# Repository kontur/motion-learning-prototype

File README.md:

#Motion learning
Prototype for wearable device enhancing motion based learning through sensory feedback.

The idea of this wearable device is to allow the wearer to rely on a multitude of additional sensory information when learning or repeating physical motion. This prototype is designed as a wrist-worn band that gives light, sound and vibration feedback.

Furthermore, the planned desktop interface allows users to record, compare and visualize their movement patterns.

##WIP
Codebase and physical design currently heavily WIP.

##Credits
Many parts of this project are based on open software or hardware. Arduino, Processing and Eagle have been used for the various aspects of the project. In more details:

* The led shield uses the [Adafruit PWM servo driver library](https://github.com/adafruit/Adafruit-PWM-Servo-Driver-Library)
* The Sparkfun IMU shields and their libraries [LSM9](https://github.com/sparkfun/LSM9DS0_Breakout) and [6DoF](https://github.com/sparkfun/IMU_Digital_Combo_Board)
* The project uses [this](http://bildr.org/2012/03/stable-orientation-digital-imu-6dof-arduino/) modification of [Varesano's FreeIMU](www.varesano.net/projects/hardware/FreeIMU) libraries for motion sensor reading
* [HSBColor](https://github.com/julioterra/HSB_Color) library for Arduino for color conversions
* [Toxiclibs](http://toxiclibs.org/) was used on the Processing visualization
* [controlP5](http://www.sojamo.de/libraries/controlP5/) was used in the Processing interface
* [Javastat](http://www2.thu.edu.tw/~wenwei/javastat/doc/) libraries were used for some portions in the software dealing with comparing motion patterns

###Authors
Johannes Neumeier, Jana Pejoska

###Acknowledgments
Project created in spring 2015 at Aalto Media Lab, in the course Prototyping Experience under guidance from Michihito Mizutani.

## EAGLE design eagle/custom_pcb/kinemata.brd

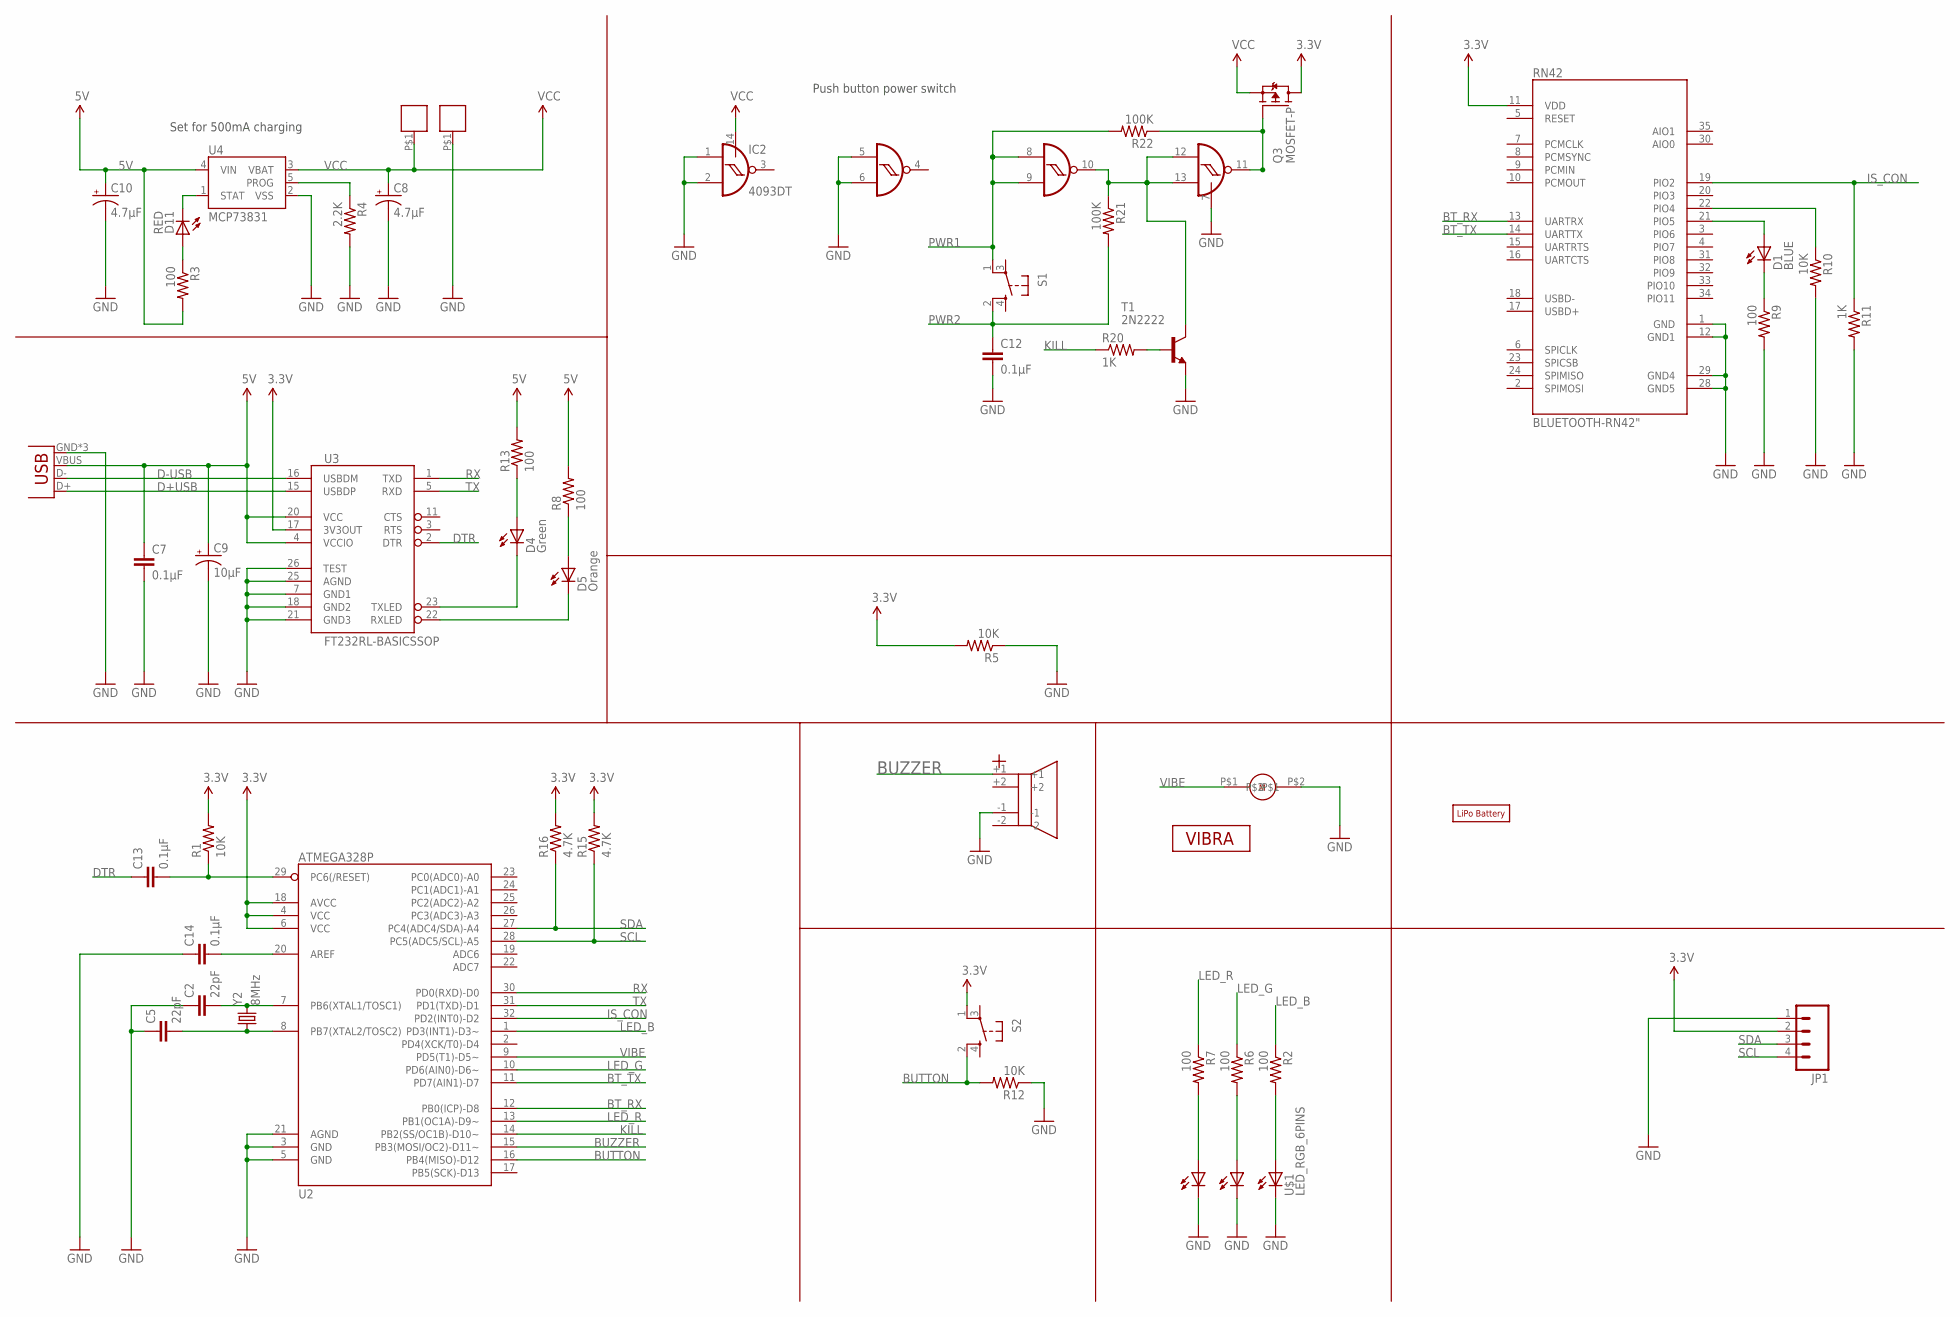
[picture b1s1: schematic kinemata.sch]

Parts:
BAT+2: LIPO_PAD
BAT-1: LIPO_PAD
C2, C5: 22pF; 1206
C7, C12, C13, C14: 0.1µF; 1206
C8, C10: 4.7µF; EIA3216
C9: 10µF; EIA3216
D1: BLUE; LED-1206
D4: Green; LED-1206
D5: Orange; LED-1206
D11: RED; LED-1206
IC2: 4093DT; MC14093B-TSSOP14
JP1: M04LONGPADS; 1X04_LONGPADS
JP6: USB-MICROB
Q3: MOSFET-P; SOT23
R1, R5, R10, R12: 10K; 1206
R2, R3, R6, R7, R8, R9, R13: 100; 1206
R4: 2.2K; 1206
R11, R20: 1K; 1206
R15, R16: 4.7K; 1206
R21, R22: 100K; 1206
RN42: BLUETOOTH-RN42"; RN42
S1, S2: TAC_SWITCH_SIDEWAY; TACTILE_SWITCH_ANGLE_SMD
T1: 2N2222; TO92-EBC-OVAL
U2: ATMEGA328P; TQFP32-08
U3: FT232RL-BASICSSOP; SSOP28DB
U4: MCP73831; SOT23-5
U$1: LED_RGB_6PINS
U$2: LIPO_BATTERY110MAH; LIPO_BATTERY_110MAH
U$3: BUZZER_4PINS; FARNELL_BUZZER_MAGNETIC_SMD_3V_2215091
U$4: VIBRATION_MOTOR_SHAPE
U$5: VIBRATION_MOTOR; VIBRATION_MOTOR_CABLE
Y2: 8MHz; CRYSTAL_8MHZ_SMD_FARNELL_2101329

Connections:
3.3V: JP1.2, Q3.3 (D), R1.2, R5.2, R15.2, R16.2, RN42.11 (VDD), S2.1 (A2), U2.4 (VCC), U2.6 (VCC), U2.18 (AVCC), U3.17 (3V3OUT)
5V: C7.1, C9.A (+), C10.A (+), JP6.VBUS, R3.2, R8.2, R13.2, U3.4 (VCCIO), U3.20 (VCC), U4.4 (VIN)
BT_RX: RN42.13 (UARTRX), U2.12 (PB0(ICP)-D8)
BT_TX: RN42.14 (UARTTX), U2.11 (PD7(AIN1)-D7)
BUTTON: R12.2, S2.2 (B2), U2.16 (PB4(MISO)-D12)
BUZZER: U2.15 (PB3(MOSI/OC2)-D11~), U$3.+1
D+USB: JP6.D+, U3.15 (USBDP)
D-USB: JP6.D-, U3.16 (USBDM)
DTR: C13.1, U3.2 (DTR)
GND: BAT-1.P$1, C2.1, C5.1, C7.2, C8.C (-), C9.C (-), C10.C (-), C12.2, C14.1, IC2.1, IC2.2, IC2.5, IC2.6, IC2.7, JP1.1, JP6.GND, JP6.MT1 (GND), JP6.MT2 (GND), R4.2, R5.1, R9.2, R10.2, R11.2, R12.1, RN42.1 (GND), RN42.12 (GND1), RN42.28 (GND5), RN42.29 (GND4), T1.E, U2.3 (GND), U2.5 (GND), U2.21 (AGND), U3.7 (GND1), U3.18 (GND2), U3.21 (GND3), U3.25 (AGND), U3.26 (TEST), U4.2 (VSS), U$1.BC, U$1.GC, U$1.RC, U$3.-1, U$5.P$2
IS_CON: R11.1, RN42.19 (PIO2), U2.32 (PD2(INT0)-D2)
KILL: R20.1, U2.14 (PB2(SS/OC1B)-D10~)
LED_B: R2.1, U2.1 (PD3(INT1)-D3~)
LED_G: R6.1, U2.10 (PD6(AIN0)-D6~)
LED_R: R7.1, U2.13 (PB1(OC1A)-D9~)
unnamed: R7.2, U$1.BA
unnamed: R2.2, U$1.GA
unnamed: D11.A, R3.1
unnamed: R6.2, U$1.RA
unnamed: D4.A, R13.1
unnamed: D5.A, R8.1
unnamed: R10.1, RN42.22 (PIO4)
unnamed: D1.A, RN42.21 (PIO5)
unnamed: C5.2, U2.8 (PB7(XTAL2/TOSC2)), Y2.P$1 (1)
unnamed: C2.2, U2.7 (PB6(XTAL1/TOSC1)), Y2.P$2 (2)
unnamed: D1.C, R9.1
unnamed: C13.2, R1.1, U2.29 (PC6(/RESET))
unnamed: C14.2, U2.20 (AREF)
unnamed: IC2.10, IC2.12, IC2.13, R21.1, T1.C
unnamed: R20.2, T1.B
unnamed: IC2.11, Q3.1 (G), R22.1
PROG: R4.1, U4.5 (PROG)
PWR1: IC2.8, IC2.9, R22.2, S1.1 (A2)
PWR2: C12.1, R21.2, S1.2 (B2)
RX: U2.30 (PD0(RXD)-D0), U3.1 (TXD)
RXLED: D5.C, U3.22 (RXLED)
SCL: JP1.4, R15.1, U2.28 (PC5(ADC5/SCL)-A5)
SDA: JP1.3, R16.1, U2.27 (PC4(ADC4/SDA)-A4)
STAT: D11.C, U4.1 (STAT)
TX: U2.31 (PD1(TXD)-D1), U3.5 (RXD)
TXLED: D4.C, U3.23 (TXLED)
VCC: BAT+2.P$1, C8.A (+), IC2.14, Q3.2 (S), U4.3 (VBAT)
VIBE: U2.9 (PD5(T1)-D5~), U$5.P$1

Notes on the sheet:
Set for 500mA charging
Push button power switch

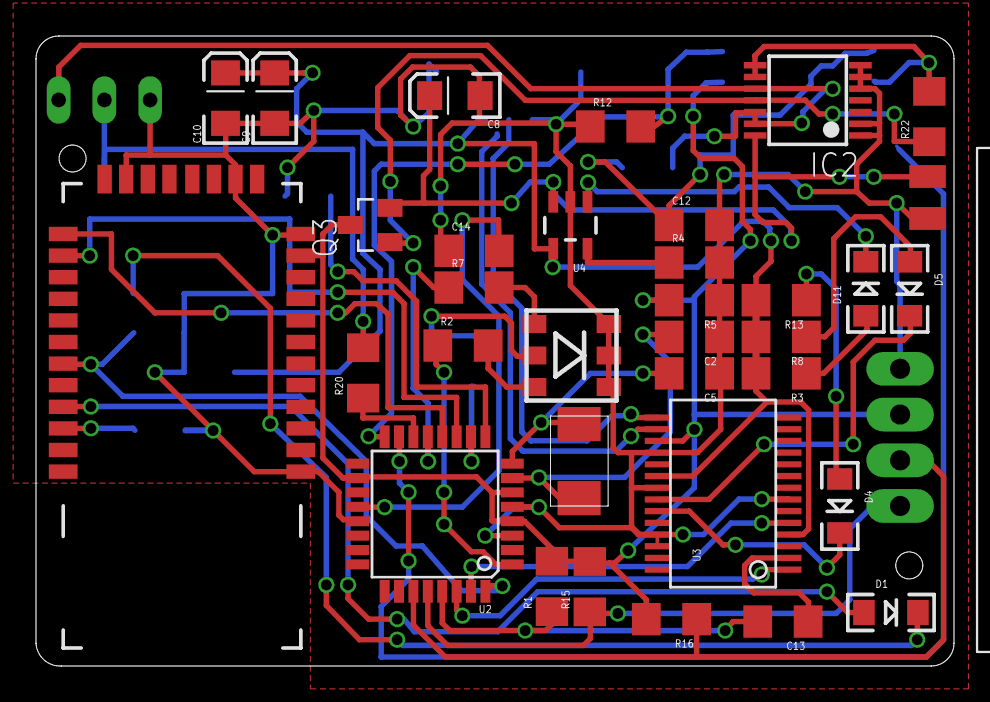
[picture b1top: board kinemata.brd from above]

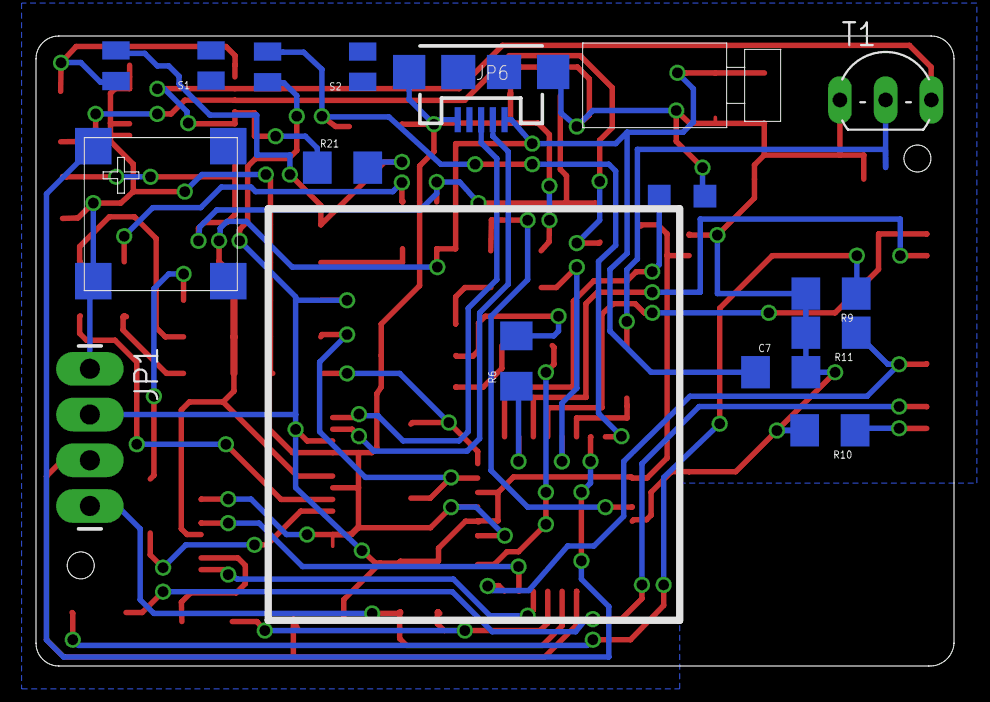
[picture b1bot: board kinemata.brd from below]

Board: 2 copper layers, 51.0 x 35.0 mm, 50 parts (14 on the bottom side), 43 nets.

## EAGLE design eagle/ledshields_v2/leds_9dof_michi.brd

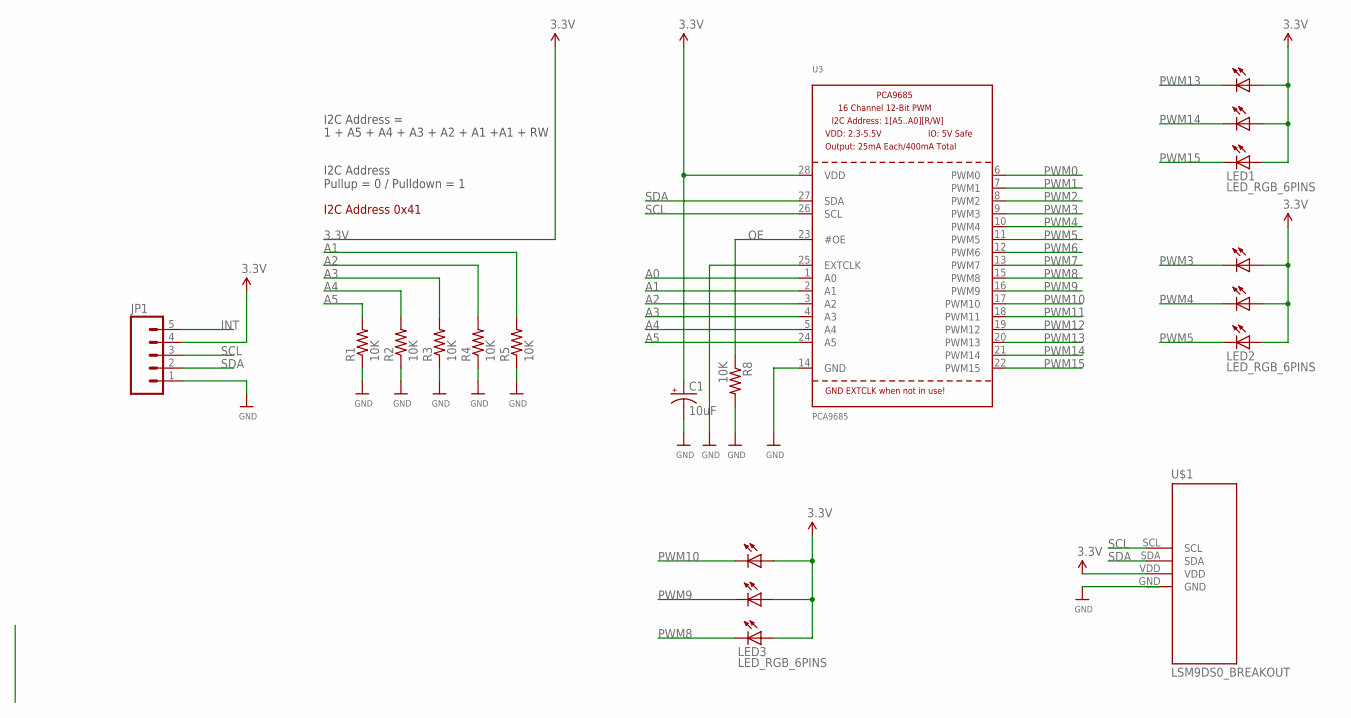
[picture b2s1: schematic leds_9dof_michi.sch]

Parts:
C1: 10uF; EIA3216
JP1: M05PTH; 1X05
LED1, LED2, LED3: LED_RGB_6PINS
R1, R2, R3, R4, R5, R8: 10K; 1206
U3: PCA9685; TSSOP28
U$1: LSM9DS0_BREAKOUT

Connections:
3.3V: C1.A (+), JP1.4, LED1.BA, LED1.GA, LED1.RA, LED2.BA, LED2.GA, LED2.RA, LED3.BA, LED3.GA, LED3.RA, U3.28 (VDD), U$1.VDD
A0: U3.1 (A0)
A1: R5.2, U3.2 (A1)
A2: R4.2, U3.3 (A2)
A3: R3.2, U3.4 (A3)
A4: R2.2, U3.5 (A4)
A5: R1.2, U3.24 (A5)
GND: C1.C (-), JP1.1, R1.1, R2.1, R3.1, R4.1, R5.1, R8.2, U3.14 (GND), U3.25 (EXTCLK), U$1.GND
INT: JP1.5
OE: R8.1, U3.23 (#OE)
PWM0: U3.6 (PWM0)
PWM1: U3.7 (PWM1)
PWM2: U3.8 (PWM2)
PWM3: LED2.BC, U3.9 (PWM3)
PWM4: LED2.RC, U3.10 (PWM4)
PWM5: LED2.GC, U3.11 (PWM5)
PWM6: U3.12 (PWM6)
PWM7: U3.13 (PWM7)
PWM8: LED3.GC, U3.15 (PWM8)
PWM9: LED3.RC, U3.16 (PWM9)
PWM10: LED3.BC, U3.17 (PWM10)
PWM11: U3.18 (PWM11)
PWM12: U3.19 (PWM12)
PWM13: LED1.BC, U3.20 (PWM13)
PWM14: LED1.RC, U3.21 (PWM14)
PWM15: LED1.GC, U3.22 (PWM15)
SCL: JP1.3, U3.26 (SCL), U$1.SCL
SDA: JP1.2, U3.27 (SDA), U$1.SDA

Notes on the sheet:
1 + A5 + A4 + A3 + A2 + A1 +A1 + RW
I2C Address =
I2C Address Pullup = 0 / Pulldown = 1
I2C Address 0x41

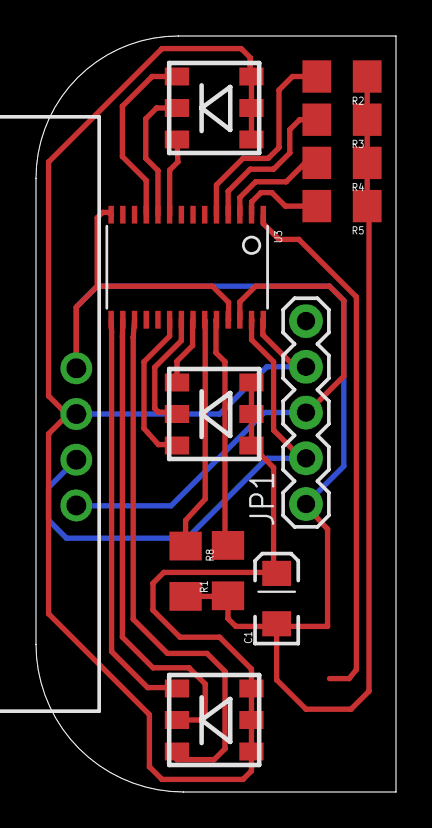
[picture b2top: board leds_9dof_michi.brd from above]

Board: 2 copper layers, 20.0 x 42.0 mm, 13 parts (0 on the bottom side), 19 nets.

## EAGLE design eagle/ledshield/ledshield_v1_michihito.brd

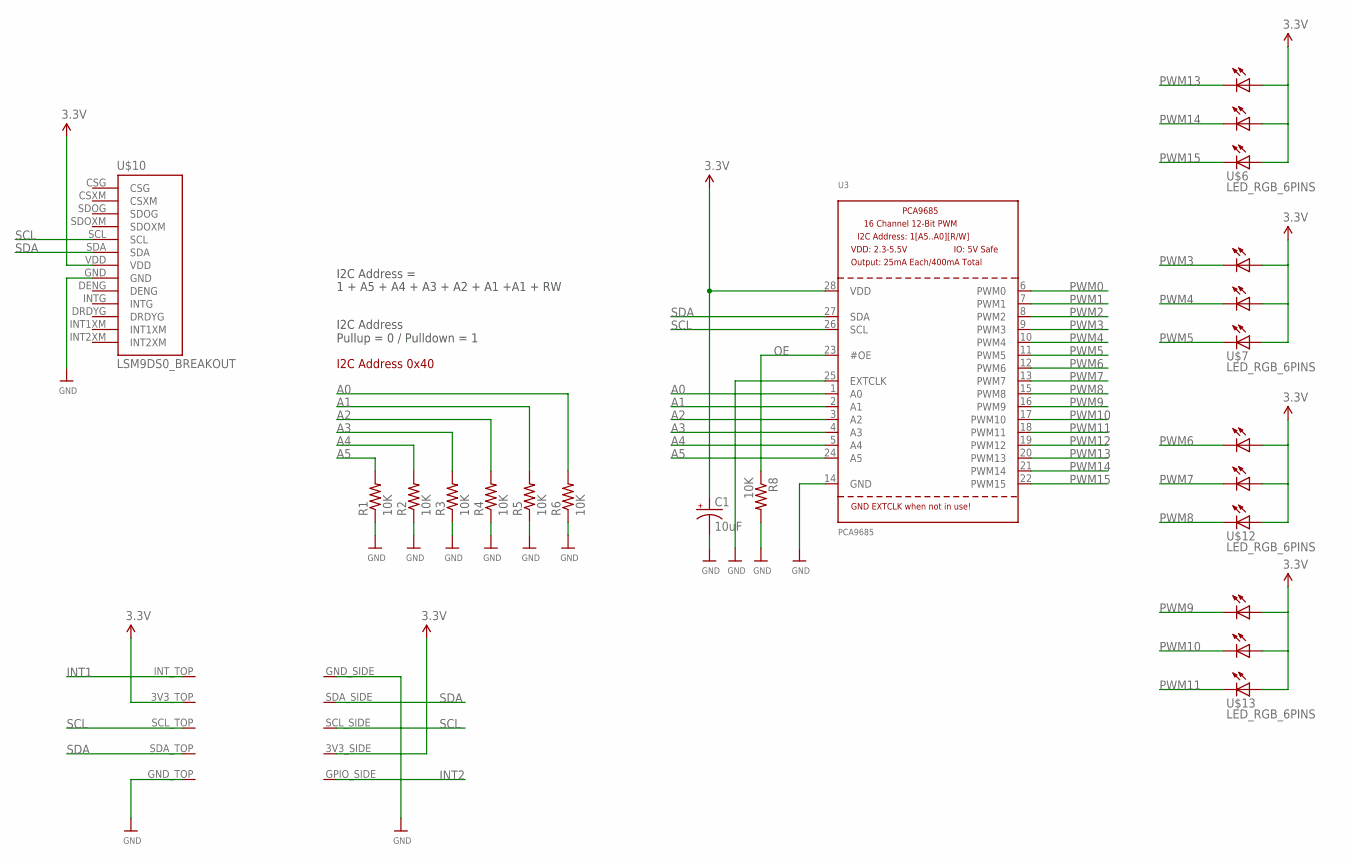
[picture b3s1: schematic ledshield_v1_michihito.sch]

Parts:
C1: 10uF; EIA3216
R1, R2, R3, R4, R5, R6, R8: 10K; 1206
U3: PCA9685; TSSOP28
U$1: IOT_MODULE_MAIN_V2_PTH; IOT_MODULE_MAIN_V3_PTH
U$6, U$7, U$12, U$13: LED_RGB_6PINS
U$10: LSM9DS0_BREAKOUT

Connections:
3.3V: C1.A (+), U3.28 (VDD), U$1.3V3_SIDE, U$1.3V3_TOP, U$6.BA, U$6.GA, U$6.RA, U$7.BA, U$7.GA, U$7.RA, U$10.VDD, U$12.BA, U$12.GA, U$12.RA, U$13.BA, U$13.GA, U$13.RA
A0: R6.2, U3.1 (A0)
A1: R5.2, U3.2 (A1)
A2: R4.2, U3.3 (A2)
A3: R3.2, U3.4 (A3)
A4: R2.2, U3.5 (A4)
A5: R1.2, U3.24 (A5)
GND: C1.C (-), R1.1, R2.1, R3.1, R4.1, R5.1, R6.1, R8.2, U3.14 (GND), U3.25 (EXTCLK), U$1.GND_SIDE, U$1.GND_TOP, U$10.GND
INT1: U$1.INT_TOP
INT2: U$1.GPIO_SIDE
OE: R8.1, U3.23 (#OE)
PWM0: U3.6 (PWM0)
PWM1: U3.7 (PWM1)
PWM2: U3.8 (PWM2)
PWM3: U3.9 (PWM3), U$7.BC
PWM4: U3.10 (PWM4), U$7.RC
PWM5: U3.11 (PWM5), U$7.GC
PWM6: U3.12 (PWM6), U$12.BC
PWM7: U3.13 (PWM7), U$12.RC
PWM8: U3.15 (PWM8), U$12.GC
PWM9: U3.16 (PWM9), U$13.BC
PWM10: U3.17 (PWM10), U$13.RC
PWM11: U3.18 (PWM11), U$13.GC
PWM12: U3.19 (PWM12)
PWM13: U3.20 (PWM13), U$6.BC
PWM14: U3.21 (PWM14), U$6.RC
PWM15: U3.22 (PWM15), U$6.GC
SCL: U3.26 (SCL), U$1.SCL_SIDE, U$1.SCL_TOP, U$10.SCL
SDA: U3.27 (SDA), U$1.SDA_SIDE, U$1.SDA_TOP, U$10.SDA

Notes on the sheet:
1 + A5 + A4 + A3 + A2 + A1 +A1 + RW
I2C Address =
I2C Address Pullup = 0 / Pulldown = 1
I2C Address 0x40

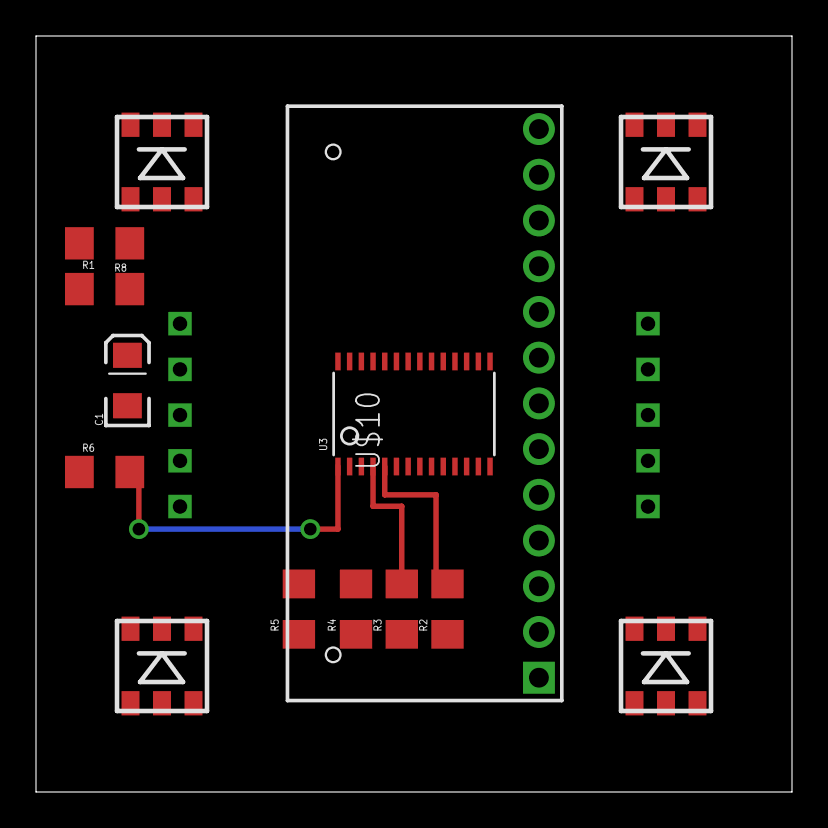
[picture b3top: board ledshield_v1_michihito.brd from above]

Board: 2 copper layers, 42.0 x 42.0 mm, 15 parts (0 on the bottom side), 23 nets.

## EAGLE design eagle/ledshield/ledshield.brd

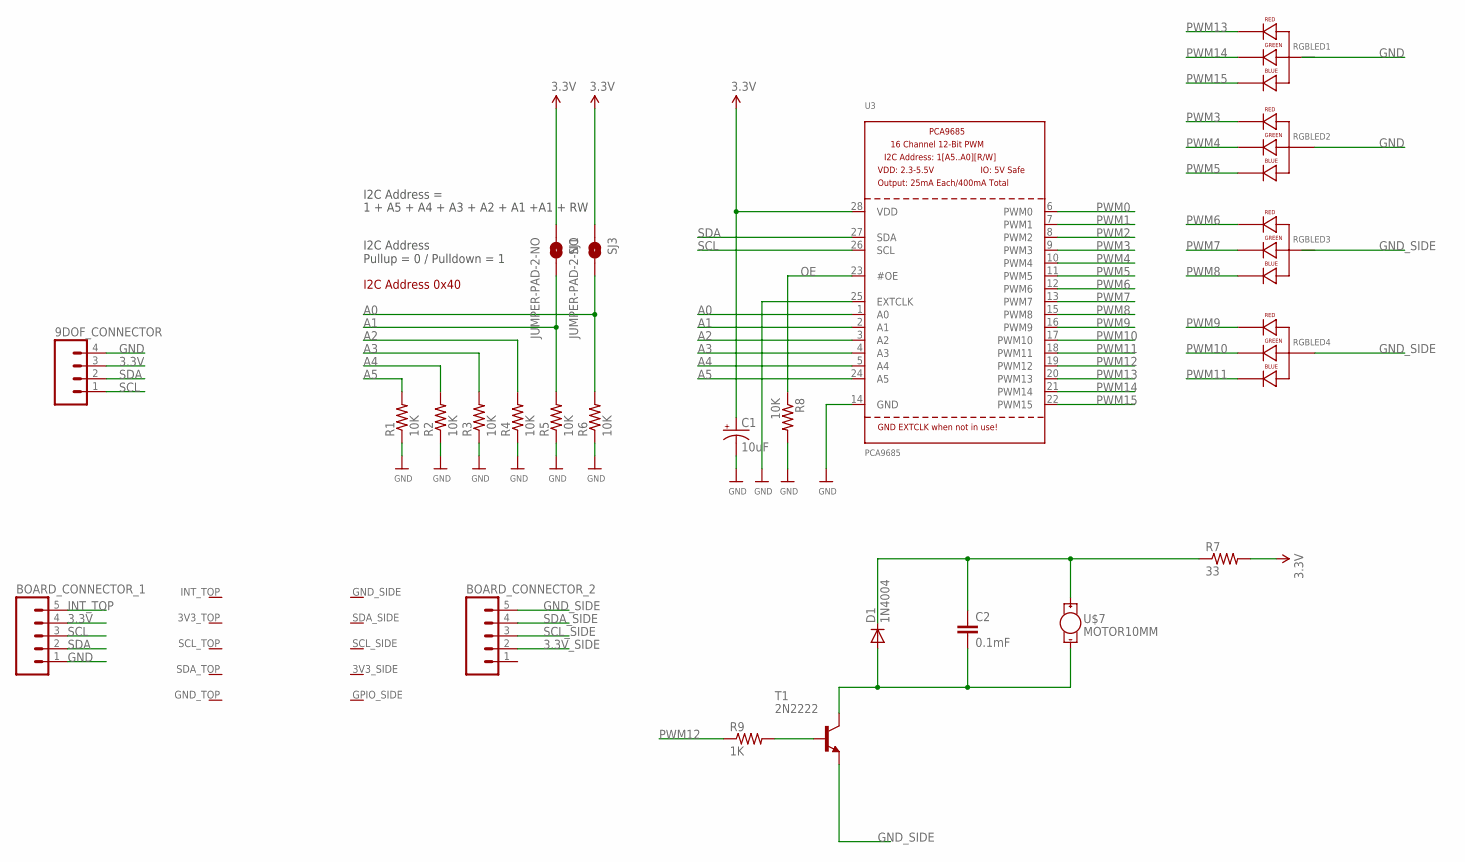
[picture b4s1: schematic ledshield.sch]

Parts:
9DOF_CONNECTOR: M041.27MM; 1X04-1.27MM
BOARD_CONNECTOR_1, BOARD_CONNECTOR_2: M051.27MM; 1X05-1.27MM
C1: 10uF; EIA3216
C2: 0.1mF; 1206
D1: 1N4004; DO41-10
R1, R2, R3, R4, R5, R6, R8: 10K; 1206
R7: 33; 1206
R9: 1K; 1206
RGBLED1, RGBLED2, RGBLED3, RGBLED4: LED-RGB-CA-THRUCLEAR; LED-RGB-THRU
SJ1, SJ3: JUMPER-PAD-2-NO; PAD-JUMPER-2-NO_NO_SILK
T1: 2N2222; TO92-EBC-OVAL
U3: PCA9685; TSSOP28
U$1: IOT_MODULE_MAIN_V2_PTH; IOT_MODULE_MAIN_V3_PTH
U$7: MOTOR10MM; VIBE-MOTOR-10MM

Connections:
3.3V: 9DOF_CONNECTOR.3, BOARD_CONNECTOR_1.4, C1.A (+), R7.2, SJ1.1, SJ3.1, U3.28 (VDD)
3.3V_SIDE: BOARD_CONNECTOR_2.2
A0: R6.2, SJ3.2, U3.1 (A0)
A1: R5.2, SJ1.2, U3.2 (A1)
A2: R4.2, U3.3 (A2)
A3: R3.2, U3.4 (A3)
A4: R2.2, U3.5 (A4)
A5: R1.2, U3.24 (A5)
GND: 9DOF_CONNECTOR.4, BOARD_CONNECTOR_1.1, C1.C (-), R1.1, R2.1, R3.1, R4.1, R5.1, R6.1, R8.2, RGBLED2.2 (ANODE), U3.14 (GND), U3.25 (EXTCLK)
GND_SIDE: BOARD_CONNECTOR_2.5, RGBLED4.2 (ANODE), T1.E
INT_TOP: BOARD_CONNECTOR_1.5
unnamed: C2.1, D1.C, R7.1, U$7.+
unnamed: C2.2, D1.A, T1.C, U$7.-
unnamed: R9.2, T1.B
OE: R8.1, U3.23 (#OE)
PWM0: U3.6 (PWM0)
PWM1: U3.7 (PWM1)
PWM2: U3.8 (PWM2)
PWM3: RGBLED2.1 (RED_CATHODE), U3.9 (PWM3)
PWM4: RGBLED2.3 (GREEN_CATHODE), U3.10 (PWM4)
PWM5: RGBLED2.4 (BLUE_CATHODE), U3.11 (PWM5)
PWM6: RGBLED3.1 (RED_CATHODE), U3.12 (PWM6)
PWM7: RGBLED3.3 (GREEN_CATHODE), U3.13 (PWM7)
PWM8: RGBLED3.4 (BLUE_CATHODE), U3.15 (PWM8)
PWM9: RGBLED4.1 (RED_CATHODE), U3.16 (PWM9)
PWM10: RGBLED4.3 (GREEN_CATHODE), U3.17 (PWM10)
PWM11: RGBLED4.4 (BLUE_CATHODE), U3.18 (PWM11)
PWM12: R9.1, U3.19 (PWM12)
PWM13: RGBLED1.1 (RED_CATHODE), U3.20 (PWM13)
PWM14: RGBLED1.3 (GREEN_CATHODE), U3.21 (PWM14)
PWM15: RGBLED1.4 (BLUE_CATHODE), U3.22 (PWM15)
SCL: 9DOF_CONNECTOR.1, BOARD_CONNECTOR_1.3, U3.26 (SCL)
SCL_SIDE: BOARD_CONNECTOR_2.3
SDA: 9DOF_CONNECTOR.2, BOARD_CONNECTOR_1.2, U3.27 (SDA)
SDA_SIDE: BOARD_CONNECTOR_2.4

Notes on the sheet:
1 + A5 + A4 + A3 + A2 + A1 +A1 + RW
I2C Address =
I2C Address Pullup = 0 / Pulldown = 1
I2C Address 0x40

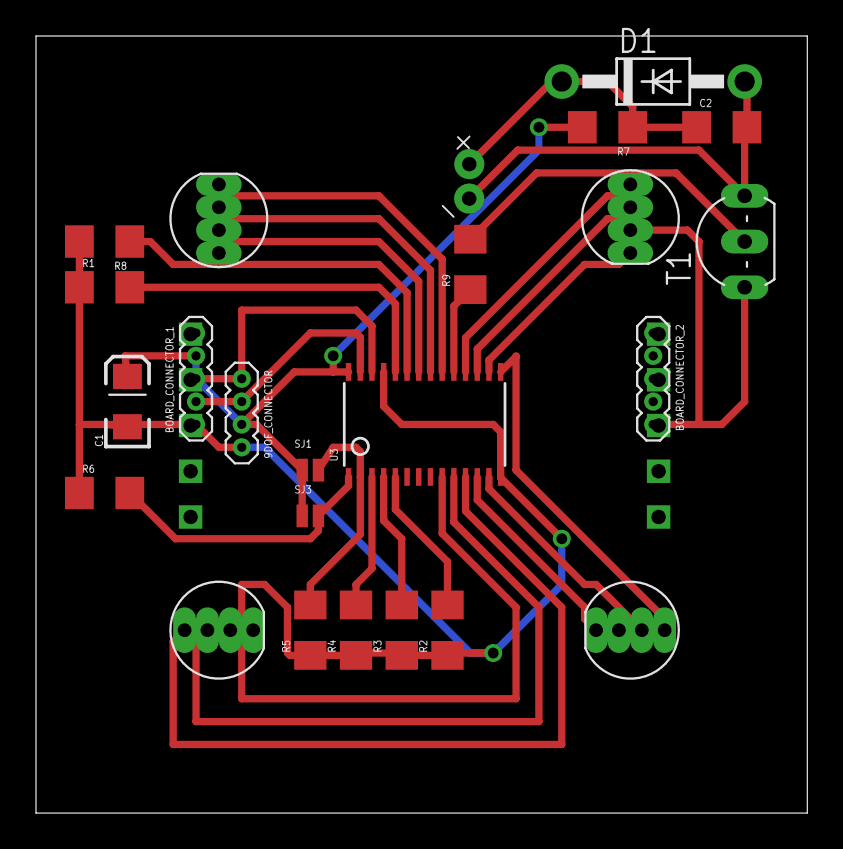
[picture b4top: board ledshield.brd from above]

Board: 2 copper layers, 42.9 x 43.2 mm, 25 parts (0 on the bottom side), 28 nets.

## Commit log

2015-03-04 basic sliders and 3d cube rotating
2015-03-04 custom 3d cube with different colored sides
2015-03-04 got basic bluetooth interface working, reading rotation values from JSON
2015-03-04 added rather messy wip arduino sketch
2015-03-04 added README.md
2015-03-07 added two arduino sketches that are useful for testing out the i2c setup
2015-03-07 switched proto to use rgb leds via i2c adafruit pwm library
2015-03-08 added first wip version of the custom led shield pcb design
2015-03-11 added basic file IO to processing sketch
2015-03-11 bluetooth device dropdownlist picker wip
2015-03-15 added fixed exampl eagle design and created second version of ledshield
2015-03-15 added bluetooth connection UI to pick device from list
2015-03-15 a bit code cleanup ;D
2015-03-15 a bit more testing on the 9dof readings and display in GUI; idle animation in GUI
2015-03-16 refined 9dof reading formatting and file saving
2015-03-16 playback modes added, more work on file saving and reading
2015-03-16 updated led shield design with common ground and passing design and electrical checks also started bluetooth/arduino communication to work in reverse from processing to arduino
2015-03-17 adding graphing class to GUI, basic hardcoded version working, WIP
2015-03-17 made the grapher more dynamically plot whatever it finds in the json, still very WIP
2015-03-18 removed external JSON package, rewrote some of the JSON stuff, added config to grapher for setting per channel color (and eventually other params)
2015-03-18 code cleanup, indentation fixes, comments
2015-03-18 fixed two missing declarations
2015-03-18 added basic cosine similarity and PCA based on javastat library, still wip with only demo data and basic test
2015-03-18 some code cleanup and documentation for similarity class
2015-03-18 some refinements to dampen value change, also removed heading from plotting for now as it clearly is ... not accurate
2015-03-18 added graph for recording and limited recording size for now, next up: comparing
2015-03-19 adding recording of pattern and match and then trying to get results from similarity class... still wip
2015-03-23 added additional dimensions to the json read and compared
2015-03-23 made grapher dimensions more configurable
2015-03-23 tried to imporve the similarity estimation
2015-03-30 added visualization wrapper that opens fullscreen on button press
2015-03-30 separate visualization test for trying around with toxilibs physics engine
2015-03-30 some more tweaking of the visualization test
2015-03-31 added 3d object to visualization example for further dev with actual 3d model included
2015-04-15 addde new arduino code based on custom lilypad + pcb and with 6dof only for now
2015-04-16 a lot more work on the 6dof proto; lights responding to roll, buzzer giving heading feedback
2015-04-19 added missing definition of tone pitches
2015-04-19 modified processing sketch for 6dof demo
2015-04-19 more tweaks and processing visualization demo working
2015-04-19 updated readme with more info and references
2015-04-23 added second version PCB design files
2015-04-27 modified 2nd version pcb designs for milling
2015-05-11 started second custom PCB arduino code
2015-05-11 added second custom PCB milling files to repo still
2015-05-11 retrospectively added milling files of 1st PCB
2015-05-13 more ground work for custom PCB version #2
2015-05-13 sensor readings are now interpreted as percentual change in respect to last reading; also, the min max values adjust dynamically to new peaks
2015-05-14 buzzer try, horrible sounding :/
2015-05-14 vibration based feedback, with fps compensation
2015-05-14 first step and try outs with new color adjusting logic
2015-05-14 color based on pitch and roll, kind of working, but with weird reset exception on extremes
2015-05-14 added basic button via bluetooth commands to processing
2015-05-14 stated continuous similarity check and analysis
2015-05-15 added test arduino sketch for testing feedback sounds
2015-05-16 first try based on percent change and timeout
2015-05-17 vibration with interrupt, loop and sensor read separation
2015-05-25 video test and preliminary include in main processing
2015-05-25 wip sound feedback via bluetooth
2015-05-26 code cleanup
2015-05-26 more code cleanup, arduino
2015-05-26 added startup and button sound
2015-05-26 some fixes, arduino and processing now work
2015-05-26 splitting up arduino loop to distribute duties within fps more evenly - WIP
2015-05-26 more work on splitting the arduino loop more evenly
2015-05-26 working with much faster sensor read loop
2015-05-26 added second 3d cube, preliminary
2015-05-26 added on screen model color to match (by value, not by appearance) to the wristband
2015-05-26 reworked UI start
2015-05-26 Processing file cleanup
2015-05-26 complete processing refactor, wip
2015-05-26 added gui for clearing recordings, more logic for recording added
2015-05-27 similarity comparison very WIP
2015-05-27 similarity kind of not working due to too slow or missin json sends from bluetooth
2015-05-27 demo buttons for video feedback
2015-05-27 feedback movie + sound working, most of the times (sometimes bluetooth send gets grabled :?)
2015-05-27 more sounds, bluetooth connect and disconnect, startup
2015-05-27 added somewhat unreliably working physical button recording
2015-05-27 fake fullscreen aka present mode
2015-05-27 some button styling
2015-05-27 fixed rotation display, and idle animation to be more random, cube sides coloring
2015-05-27 fixed top graph not working
2015-05-27 update graphs during recording of either track
2015-05-27 recording visual highlight on frame of the respective track
2015-05-27 added delayed sound execution for feedback
2015-05-27 doh... forgetten to add a whole bunch of files for a while :/
2015-05-27 added progress video display for recording phase
2015-05-27 added recording start and stop sounds with blatant delay pausing the sketch
2015-05-27 added some missing arduino files and an arduino buzzer sound testing example
2015-09-25 started work on new custom board
2015-09-25 some more initial work on the custom PCB
2015-09-29 custom pcb further routed
2015-09-30 custom PCB wiring technically done, DRC ok
2015-10-05 0.012 wiring almost done
2015-10-06 custom pcb wiring passing drc
2015-10-12 tweaked positioning and minor issues on custom PCB
2015-10-21 custom pcb pre print
2016-01-25 some cleanup
2016-01-25 added some arduino helpers
2016-01-25 added second version led shields
2016-01-25 added eagle design files for v4 prototype PCB
2016-01-25 added 3d design files for kinemata v4
2016-01-25 arduino code for v4 started
2016-01-25 started new processing v4
2016-01-25 renamed current WIP files to Kinemata for each part of the project
2016-01-25 arduino to processing BT working for one device; new processing UI started
2016-01-25 pde tested and working for two BT connections
2016-01-26 more cleanup, more gui work
2016-01-26 more UI and BT connect stuff
2016-01-26 added missing sliders to ui, not hooked up to bluetooth data yet
2016-01-27 more work on bluetooth connection and handling; improvement to raw send speed from Arduino to Processing
2016-01-27 more bt and grapher tweaks
2016-01-28 slightly tweaked 3d modle for bottom - screw positioning
2016-02-03 wip implementing option to recording and save all tracks at once
2016-02-03 record UI implementation WIP, also for linked tracks
2016-02-05 stared file saving csv
2016-02-08 grapher toggle from checkboxes wip
2016-02-14 some fixes for 3.0.2 and checkboxes wip
2016-02-14 added button icons
2016-02-14 button highlight for unsaved recording
2016-02-14 link slider checkboxes with grapher display
2016-02-15 preliminary overlay implementation
2016-02-15 fixed error in slider checkbox and made both tracks responsive to respective checkboxes
2016-02-15 filename automatic with datetime
2016-02-16 fixed overlay somewhat
2016-02-16 code clean up and refactoring
2016-02-16 added vibration to data json and fixed file save csv data ordering bug
2016-02-16 added BT dps meter and improved arduino FPS slightly
2016-02-16 small arduino ammend
2016-02-17 Added method call delegator (Processing workaround) and a bunch of code commenting, esp. Kinemata.pde
2016-02-17 recording state button changes and filename checks
2016-02-17 removed delegator class, implemented more direct 'processing' way of doing the same
2016-02-17 colored 3d box again
2016-02-18 implemented recording same consecutive frames as empty, slider colors match grapher
2016-02-18 fixed bluetooth connecting overlay rendering
2016-02-19 wip overlay
2016-02-19 fixed overlay, again
2016-02-19 inverted pitch and roll on sensor side - the sensor in the new version is oriented differentlygit status
2016-02-19 fixed button unresponsive / layering issue
2016-02-19 couple of obvious fixes to separate track recording mode
2016-02-20 fixed the implemented pitch/roll reverse to not affect light calculations, also removed any serial.prints on device which further sped up the processing
2016-02-20 fixed connection FPS display
2016-02-20 ignore exported application files from git
2016-02-20 small tweaks gor 3d cube display and rendering
2016-02-20 small ammend to BT connection close GUI update

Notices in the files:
parts and their libraries:
SparkFun-Passives: Licensing: Creative Commons ShareAlike 4.0 International - https://creativecommons.org/licenses/by-sa/4.0
SparkFun-Resistors: Licensing: CC v3.0 Share-Alike You are welcome to use this library for commercial purposes.
